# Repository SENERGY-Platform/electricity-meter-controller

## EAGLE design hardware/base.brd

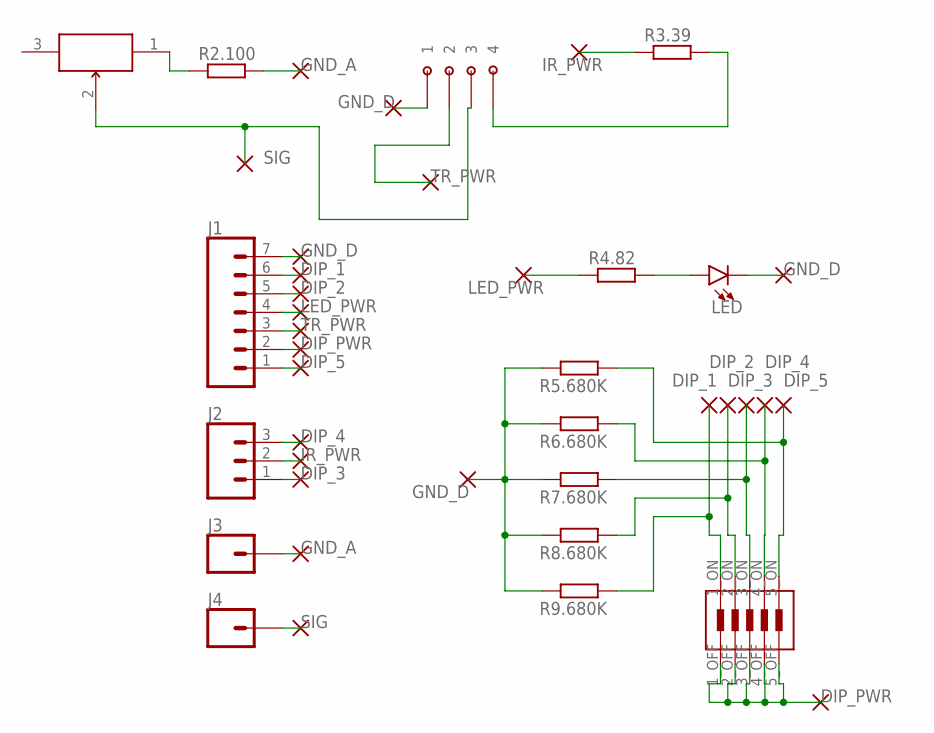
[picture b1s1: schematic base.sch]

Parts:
J1: CONN_07; 1X07
J2: CONN_03; 1X03
J3, J4: CONN_01; 1X01
LED: LED-3MM-NO_SILK; LED_3MM-NS
R2.100, R3.39, R4.82, R5.680K, R6.680K, R7.680K, R8.680K, R9.680K: R-EU_0204/7; 0204/7
U$1: DF1BZ-4DP-2.5DS
U$2: DIP-SW-CTS-208-5
U$3: CT6EP103

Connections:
DIP_1: J1.6, R9.680K.1, U$2.1_ON
DIP_2: J1.5, R8.680K.1, U$2.2_ON
DIP_3: J2.1, R7.680K.1, U$2.3_ON
DIP_4: J2.3, R6.680K.1, U$2.4_ON
DIP_5: J1.1, R5.680K.1, U$2.5_ON
DIP_PWR: J1.2, U$2.1_OFF, U$2.2_OFF, U$2.3_OFF, U$2.4_OFF, U$2.5_OFF
GND_A: J3.1, R2.100.2
GND_D: J1.7, LED.K (C), R5.680K.2, R6.680K.2, R7.680K.2, R8.680K.2, R9.680K.2, U$1.1
IR_PWR: J2.2, R3.39.1
LED_PWR: J1.4, R4.82.1
unnamed: R2.100.1, U$3.1
unnamed: R3.39.2, U$1.4
unnamed: LED.A, R4.82.2
P$1: U$3.3
SIG: J4.1, U$1.3, U$3.2
TR_PWR: J1.3, U$1.2

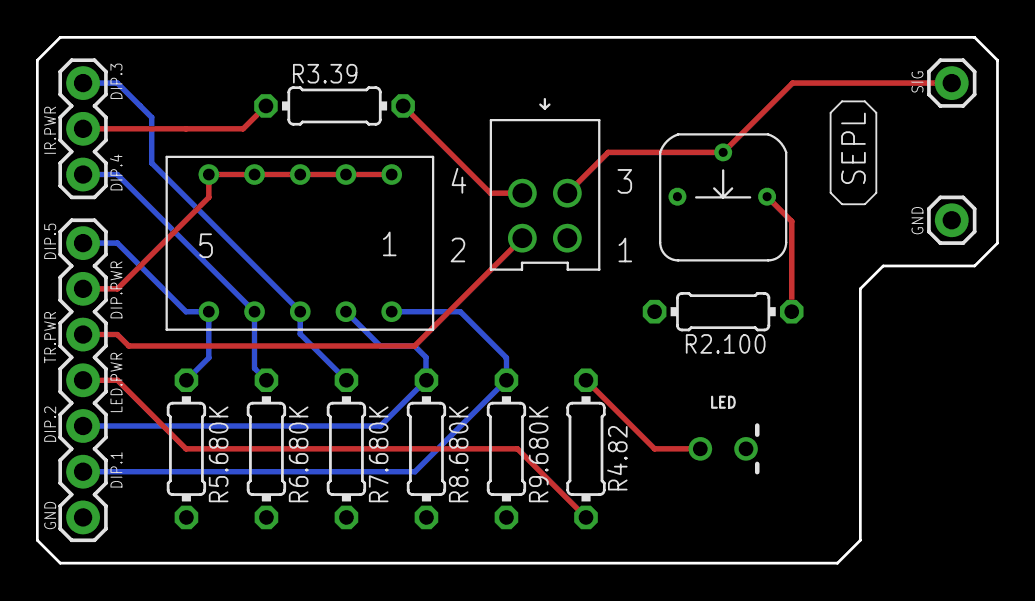
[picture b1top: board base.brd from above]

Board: 2 copper layers, 53.3 x 29.2 mm, 16 parts (0 on the bottom side), 15 nets.

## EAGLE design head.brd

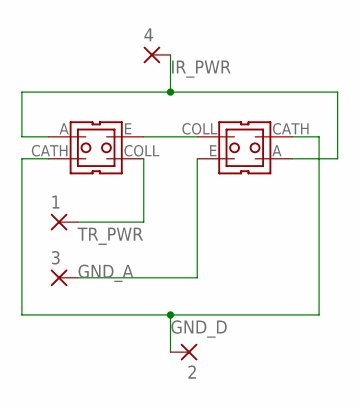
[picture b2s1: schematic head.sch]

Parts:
1, 2, 3, 4: 2,15/1,0
U$1, U$2: CNY70

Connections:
GND_A: 3.1, U$2.E (GND(PWR))
GND_D: 2.1, U$1.CATH (GND(DIG)), U$2.CATH (GND(DIG))
IR_PWR: 4.1, U$1.A (5V(DIG)), U$2.A (5V(DIG))
unnamed: U$1.E (GND(PWR)), U$2.COLL (5V(PWR))
TR_PWR: 1.1, U$1.COLL (5V(PWR))

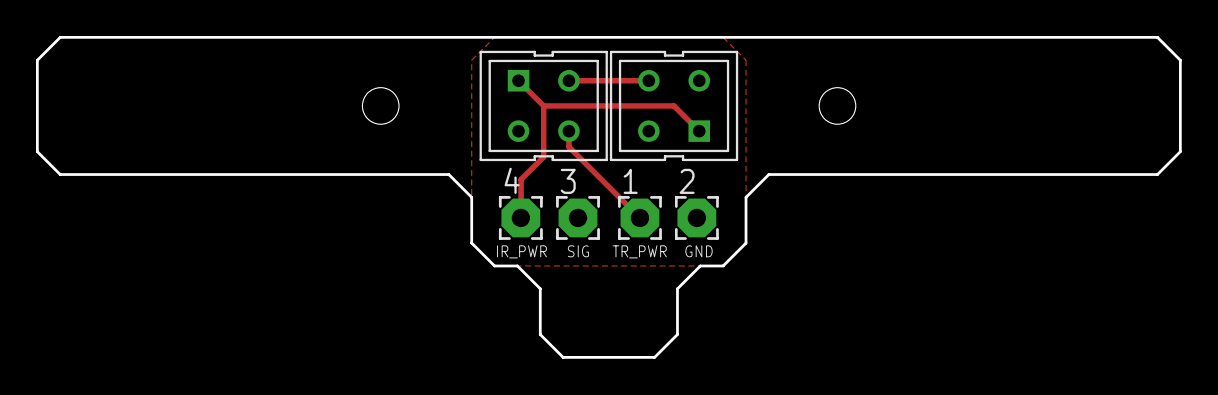
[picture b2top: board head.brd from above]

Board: 2 copper layers, 63.5 x 17.8 mm, 6 parts (0 on the bottom side), 5 nets.

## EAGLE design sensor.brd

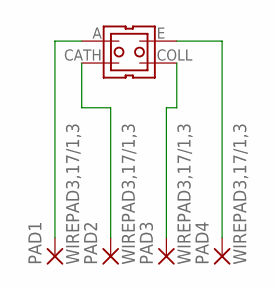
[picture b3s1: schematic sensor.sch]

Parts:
PAD1, PAD2, PAD3, PAD4: WIREPAD3,17/1,3; 3,17/1,3
U$1: CNY70

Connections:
unnamed: PAD1.1, U$1.A (5V(DIG))
unnamed: PAD2.1, U$1.CATH (GND(DIG))
unnamed: PAD4.1, U$1.E (GND(PWR))
unnamed: PAD3.1, U$1.COLL (5V(PWR))

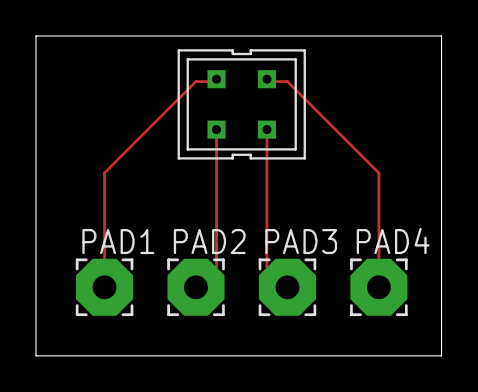
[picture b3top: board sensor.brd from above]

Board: 2 copper layers, 22.5 x 17.8 mm, 5 parts (0 on the bottom side), 4 nets.

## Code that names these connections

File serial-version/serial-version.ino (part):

const int signal_pin = A0;
const int ir_pwr_pin = 6;
const int dip_pwr_pin = 9;
const int tr_pwr_pin = 10;
const int led_pwr_pin = 11;
const char sw_version[] = "2.12.0";

struct pdcm {
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  }

  // set pins
  pinMode(ir_pwr_pin, OUTPUT);
  pinMode(led_pwr_pin, OUTPUT);
  pinMode(dip_pwr_pin, OUTPUT);
  pinMode(tr_pwr_pin, OUTPUT);
  setupDipPins(dip_pins, sizeof(dip_pins));

  // print start message
  delay(2000);
  readDips(&dip_pwr_pin, dip_pins, sizeof(dip_pins));
  delay(500);
  blinkLED(&led_pwr_pin, 1, 500);
  Serial.print(F("FERRARIS-SENSOR:V"));
  Serial.print(sw_version);
  Serial.print(":");
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int reading_no_ambient;
float rema = 0.0;

void initSmoother(const int *signal_pin, const int *ir_pwr_pin, int pause=1800) {
  digitalWrite(*ir_pwr_pin, HIGH);
  delayMicroseconds(pause);
  reading_ir = analogRead(*signal_pin);
  digitalWrite(*ir_pwr_pin, LOW);
  delayMicroseconds(pause);
  rema = static_cast<float>(reading_ir - analogRead(*signal_pin));
}

int noAmbientSmoothedRead(const int *signal_pin, const int *ir_pwr_pin, int pause=1800, float multi=0.003) {
  digitalWrite(*ir_pwr_pin, HIGH);
  delayMicroseconds(pause);
  reading_ir = analogRead(*signal_pin);
  digitalWrite(*ir_pwr_pin, LOW);
  delayMicroseconds(pause);
  reading_no_ambient = reading_ir - analogRead(*signal_pin);
  rema = rema + (reading_no_ambient - rema) * snapCurve(abs(reading_no_ambient - rema) * multi);
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void getCommand() {
  command = readLine();
  if (command != "") {
    blinkLED(&led_pwr_pin);
  }
}


void manualRead(int pause=50) {
  digitalWrite(tr_pwr_pin, HIGH);
  initSmoother(&signal_pin, &ir_pwr_pin);
  if (pause > 0) {
    while (command != "STP") {
      getCommand();
      Serial.println(noAmbientSmoothedRead(&signal_pin, &ir_pwr_pin));
      delay(pause);
    }
  } else {
    while (command != "STP") {
      getCommand();
      Serial.println(noAmbientSmoothedRead(&signal_pin, &ir_pwr_pin));
    }
  }
  digitalWrite(tr_pwr_pin, LOW);
}


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int reading;

void findBoundaries() {
  digitalWrite(tr_pwr_pin, HIGH);
  int left_edge = -100;
  int right_edge = 0;
  initSmoother(&signal_pin, &ir_pwr_pin);
  while (command != "STP") {
    getCommand();
    reading = noAmbientSmoothedRead(&signal_pin, &ir_pwr_pin);
    if (left_edge == -100) {
      left_edge = reading;
    }
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      right_edge = reading;
    }
  }
  digitalWrite(tr_pwr_pin, LOW);
  Serial.print(left_edge);
  Serial.print(F(":"));
  Serial.println(right_edge);
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      int mid;
      int l_pos;
      int r_pos;
      digitalWrite(tr_pwr_pin, HIGH);
      initSmoother(&signal_pin, &ir_pwr_pin);
      while (command != "STP") {
        getCommand();
        reading = noAmbientSmoothedRead(&signal_pin, &ir_pwr_pin);
        l_pos = 0;
        r_pos = resolution - 1;
        while (l_pos <= r_pos) {
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          }
        }
      }
      digitalWrite(tr_pwr_pin, LOW);
      for (int bin = 0; bin < resolution; bin++) {
        Serial.print(histogram[bin][0]);
          Serial.print(":");
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//right_boundary = conf_b

void intervalDetection() {
  digitalWrite(tr_pwr_pin, HIGH);
  bool detected = false;
  int detection_threshold_count = 0;
  int no_detection_threshold_count = 0;
  unsigned long current_ms;
  unsigned long last_loop = 0;
  initSmoother(&signal_pin, &ir_pwr_pin);
  while (command != "STP") {
    current_ms = millis();
    reading = noAmbientSmoothedRead(&signal_pin, &ir_pwr_pin);
    if (reading >= conf_a && reading <= conf_b) {
      if (detection_threshold_count < detection_threshold) {
        detection_threshold_count++;
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        no_detection_threshold_count = 0;
        if (detected == false) {
          detected = true;
          digitalWrite(led_pwr_pin, HIGH);
          Serial.println(F("DET"));
        }
      }
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          no_detection_threshold_count = 0;
          detection_threshold_count = 0;
          detected = false;
          digitalWrite(led_pwr_pin, LOW);
        }
      } else {
        detection_threshold_count = 0;
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    if (current_ms - last_loop > 5000) {
      last_loop = current_ms;
      if (detected != true) {
        blinkLED(&led_pwr_pin, 1, 0);
      }
    }
    /* debug
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    Serial.println(no_detection_threshold_count);
    */
  }
  digitalWrite(tr_pwr_pin, LOW);
}


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//lower_limit_distance = conf_b

void averageDetection() {
  digitalWrite(tr_pwr_pin, HIGH);
  bool detected = false;
  int detection_threshold_count = 0;
  int no_detection_threshold_count = 0;
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  long iteration = 1;
  unsigned long current_ms;
  unsigned long last_loop = 0;
  initSmoother(&signal_pin, &ir_pwr_pin);
  while (command != "STP") {
    current_ms = millis();
    reading = noAmbientSmoothedRead(&signal_pin, &ir_pwr_pin);
    if (calibrated == true) {
      if (reading <= (current_avg - conf_b)) {
        if (detection_threshold_count < detection_threshold) {
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            no_detection_threshold_count = 0;
            detection_threshold_count = 0;
            detected = false;
            blinkLED(&led_pwr_pin);
          }
        } else {
          detection_threshold_count = 0;
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    getCommand();
    if (current_ms - last_loop > 5000) {
      last_loop = current_ms;
      blinkLED(&led_pwr_pin, 1, 0);
    }
  }
  digitalWrite(tr_pwr_pin, LOW);
}


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
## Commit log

2018-01-22 added vars
2018-01-22 added startup messages and mqtt client
2018-01-23 fixed keepalive and message
2018-01-23 added ntp and refactor
2018-01-23 working implementation
2018-01-23 added LED feedback
2018-01-25 fixed bugs
2018-01-25 disable LED to avoid errors in dark envs
2018-01-29 added reset on failure and more LED feedback
2018-02-01 refactor and reduced dynamic memory footprint by 20%
2018-02-01 more refactoring and further reduction of memory footprint
2018-02-01 refactor, added denoised readout and fixed bug
2018-02-01 added debug output
2018-02-02 refactor
2018-02-26 changed ntp server
2018-02-27 split id and topic
2018-02-28 changed original to eth version
2018-02-28 added serial version
2018-02-28 added wifi version for wifi (ESP8266)
2018-02-28 changed file names
2018-02-28 removed unused variable
2018-02-28 added circuit
2018-03-01 added dip switch ID
2018-03-02 removed default values
2018-03-07 fixed
2018-03-15 fixes and added visual feedback
2018-03-15 init
2018-03-21 changed routing
2018-03-21 no message
2018-03-26 init dual sensor version
2018-03-27 updated for new circuit
2018-03-28 added parts list
2018-04-03 changes for new pin layout
2018-04-03 multiple detection prevention
2018-04-09 adjusted for new PCB
2018-04-09 added cable
2018-04-09 changed parts
2018-04-09 updated layout and part
2018-04-11 updated with vat
2018-04-11 added aisler links
2018-04-30 changed pins
2018-05-14 added serial output, fixes
2018-05-14 refactor and implemented multiple detection protection
2018-05-15 rm debug lines
2018-05-15 added find lowest value
2018-05-15 revert to longer delay
2018-05-15 longer delay
2018-05-15 remove last detection delay
2018-05-15 updated drills and pads
2018-05-15 revert to old lib
2018-05-15 updated for new part
2018-05-16 fixes
2018-05-17 negative detection, FE mode and refactor
2018-05-17 added protection for values getting to large
2018-05-18 changed delays
2018-05-22 refactor and start of implementation
2018-05-23 implemented bin search for value distribution
2018-05-23 working detection
2018-05-28 added general conf
2018-05-28 user char array for ID
2018-05-28 switched to number ID
2018-05-29 added RES command
2018-06-02 changed behavior
2018-06-04 reverted back to letters instead of numbers
2018-06-13 use numbers for ID
2018-07-23 implemented responsive exponential moving average for smoothed readings, added greeting, performance tweaks
2018-07-23 commented debug lines
2018-07-23 fix ready bug
2018-07-23 testing
2018-07-24 fixed initial rema value for small multipliers
2018-07-24 set to highest possible baud rate
2018-07-24 updated manualRead for readings without delay
2018-07-24 tighter delays for faster startup and moved RDY message to main loop
2018-09-05 project refactor
2018-09-12 refactor, added license info
2018-10-18 changed header

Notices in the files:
parts and their libraries:
SparkFun-Connectors: Licensing: Creative Commons ShareAlike 4.0 International - https://creativecommons.org/licenses/by-sa/4.0
